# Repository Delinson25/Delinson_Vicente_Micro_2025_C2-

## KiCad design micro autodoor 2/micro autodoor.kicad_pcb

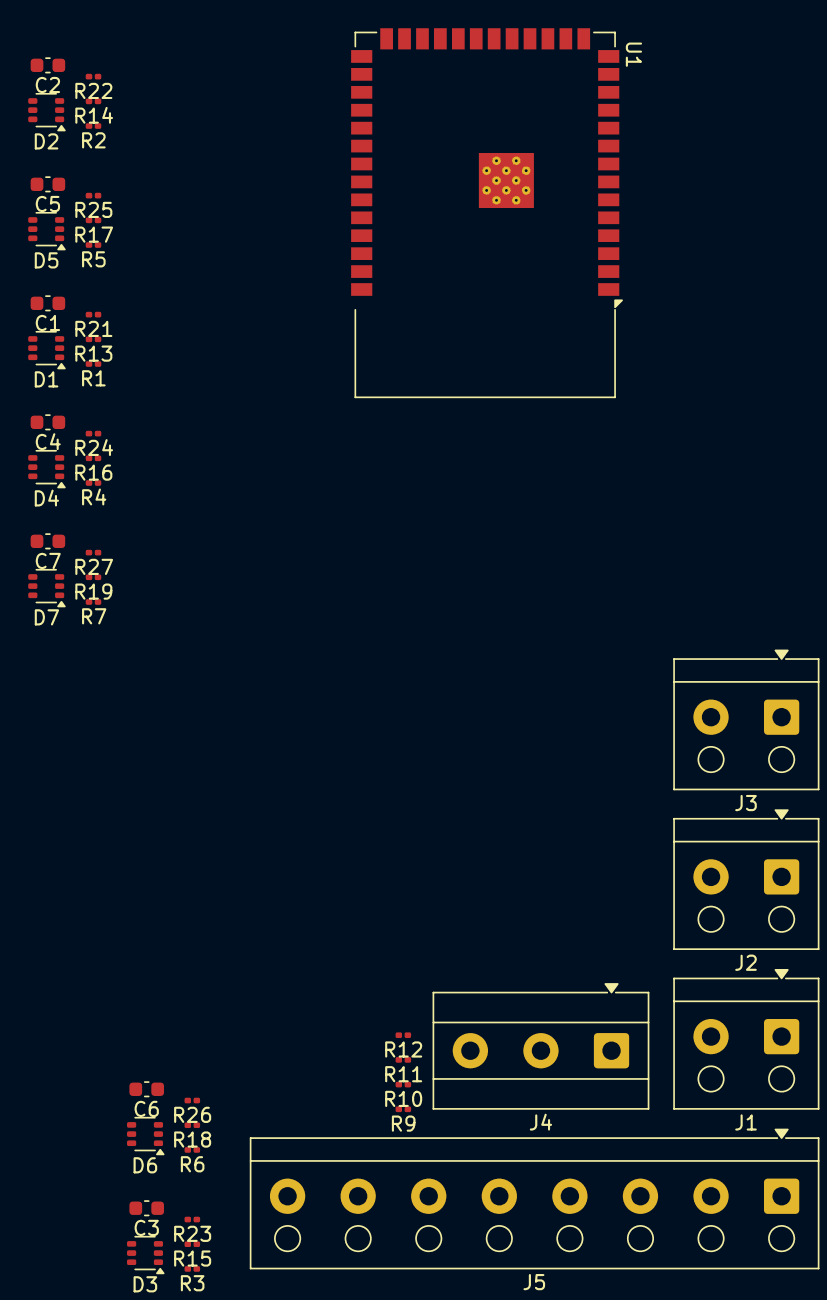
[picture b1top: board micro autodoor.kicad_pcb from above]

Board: 2 copper layers, 45 parts (0 on the bottom side), 16 nets, no tracks yet.

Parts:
C1, C2, C3, C4, C5, C6, C7: 100nF; C_0603_1608Metric
D1, D2, D3, D4, D5, D6, D7: PESD3V3L5UY; SOT-363_SC-70-6
J1, J2, J3: Screw_Terminal_01x02; TerminalBlock_RND_205-00001_1x02_P5.00mm_Horizontal
J4: Screw_Terminal_01x03; TerminalBlock_MetzConnect_Type055_RT01503HDWU_1x03_P5.00mm_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
J5: Screw_Terminal_01x08; TerminalBlock_RND_205-00007_1x08_P5.00mm_Horizontal
R1, R2, R3, R4, R5, R6, R7, R21, R22, R23, R24, R25, R26, R27: 10k; R_0201_0603Metric
R9, R10, R11, R12: 22K; R_0201_0603Metric
R13, R14, R15, R16, R17, R18, R19: 100; R_0201_0603Metric
U1: ESP32-S3-WROOM-1

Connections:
+3.3V: R1.1, R2.1, R3.1, R4.1, R5.1, R6.1, R7.1, R9.1, R10.1, R11.1, R12.1, U1.2 (3V3)
/board_principal/BA: J5.4, R4.2, R16.2
/board_principal/BC: J5.3, R5.2, R17.2
/board_principal/B_STOP: J5.2, R6.2, R18.2
/board_principal/FTC: J5.1, R7.2, R19.2
/board_principal/IMPUT_DIGITAL1/IN: R2.2, R14.2
/board_principal/IMPUT_DIGITAL1/OUT: C2.1, D2.1 (K1), R14.1, R22.1
/board_principal/IMPUT_DIGITAL2/OUT: C3.1, D3.1 (K1), R15.1, R23.1
/board_principal/IMPUT_DIGITAL3/OUT: C4.1, D4.1 (K1), R16.1, R24.1
/board_principal/IMPUT_DIGITAL4/OUT: C5.1, D5.1 (K1), R17.1, R25.1
/board_principal/IMPUT_DIGITAL5/OUT: C6.1, D6.1 (K1), R18.1, R26.1
/board_principal/IMPUT_DIGITAL6/OUT: C7.1, D7.1 (K1), R19.1, R27.1
/board_principal/IMPUT_DIGITAL/IN: R1.2, R13.2
/board_principal/IMPUT_DIGITAL/OUT: C1.1, D1.1 (K1), R13.1, R21.1
/board_principal/PP: J5.5, R3.2, R15.2
GND: C1.2, C2.2, C3.2, C4.2, C5.2, C6.2, C7.2, D1.2 (A), D2.2 (A), D3.2 (A), D4.2 (A), D5.2 (A), D6.2 (A), D7.2 (A), J3.2, J4.2, J5.8, R21.2, R22.2, R23.2, R24.2, R25.2, R26.2, R27.2, U1.1 (GND), U1.40 (GND), U1.41 (GND)

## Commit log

2025-06-12 codigo porton
2025-06-27 Rename codigo porton to codigo porton.c
2025-06-27 Rename codigo porton.c to Maquina de estado.c
